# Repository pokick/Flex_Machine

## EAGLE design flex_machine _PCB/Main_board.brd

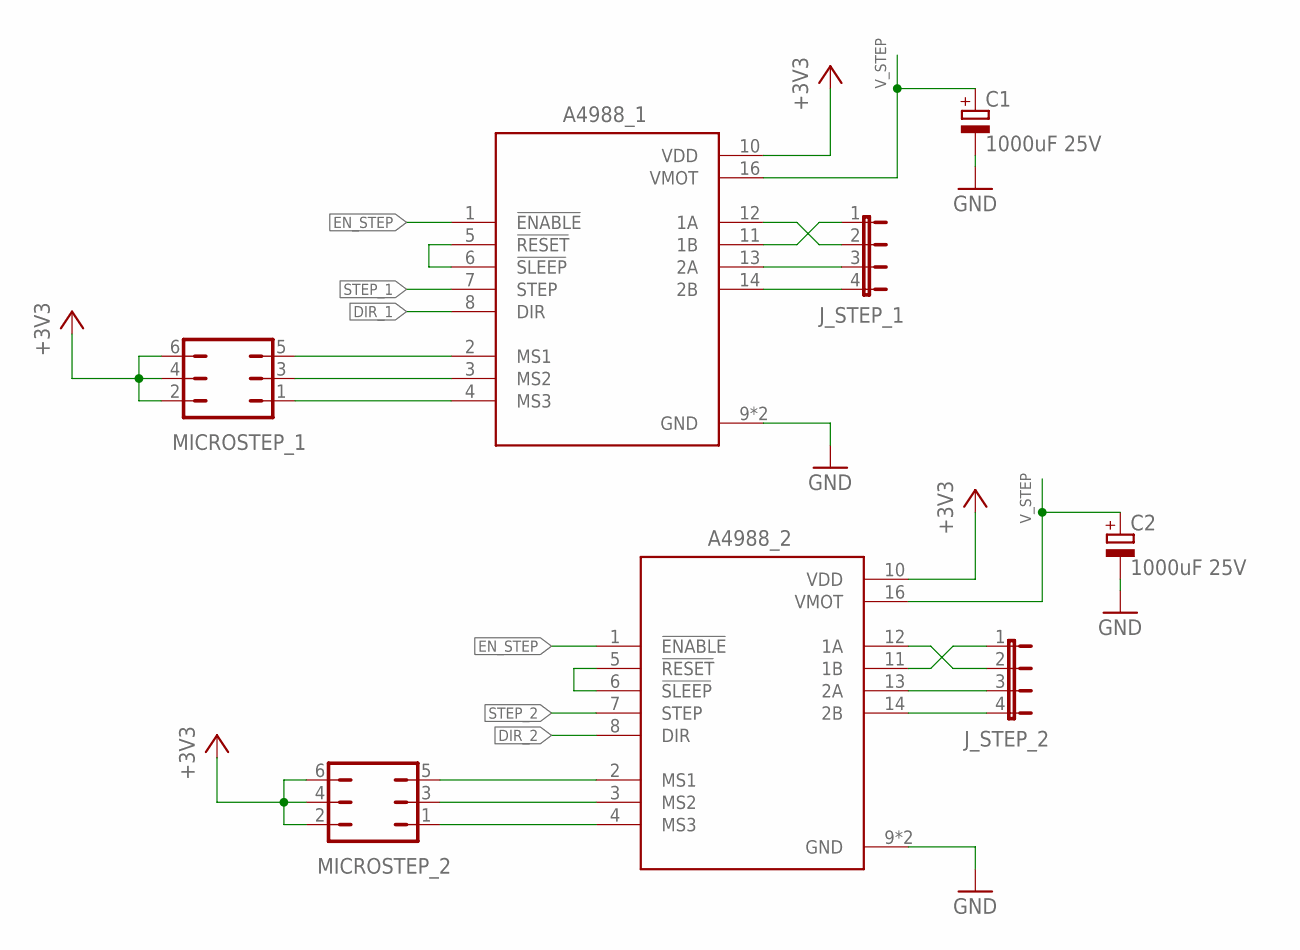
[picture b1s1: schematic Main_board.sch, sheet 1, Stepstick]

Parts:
A4988_1, A4988_2: A4988_STEPPER_MOTOR_DRIVER_CARRIER; MODULE_A4988_STEPPER_MOTOR_DRIVER_CARRIER
C1, C2: 1000uF 25V; E3,5-10
J_STEP_1, J_STEP_2: JP4E; JP4
MICROSTEP_1, MICROSTEP_2: JP3Q

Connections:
+3V3: A4988_1.10 (VDD), A4988_2.10 (VDD), MICROSTEP_1.2, MICROSTEP_1.4, MICROSTEP_1.6, MICROSTEP_2.2, MICROSTEP_2.4, MICROSTEP_2.6; also elsewhere on the board
DIR_1: A4988_1.8 (DIR); also elsewhere on the board
DIR_2: A4988_2.8 (DIR); also elsewhere on the board
EN_STEP: A4988_1.1 (!ENABLE), A4988_2.1 (!ENABLE); also elsewhere on the board
GND: A4988_1.9 (GND), A4988_1.15 (GND), A4988_2.9 (GND), A4988_2.15 (GND), C1.-, C2.-; also elsewhere on the board
unnamed: A4988_1.5 (!RESET), A4988_1.6 (!SLEEP)
unnamed: A4988_1.2 (MS1), MICROSTEP_1.5
unnamed: A4988_1.3 (MS2), MICROSTEP_1.3
unnamed: A4988_1.4 (MS3), MICROSTEP_1.1
unnamed: A4988_1.11 (1B), J_STEP_1.1
unnamed: A4988_1.12 (1A), J_STEP_1.2
unnamed: A4988_1.13 (2A), J_STEP_1.3
unnamed: A4988_1.14 (2B), J_STEP_1.4
unnamed: A4988_2.2 (MS1), MICROSTEP_2.5
unnamed: A4988_2.3 (MS2), MICROSTEP_2.3
unnamed: A4988_2.4 (MS3), MICROSTEP_2.1
unnamed: A4988_2.5 (!RESET), A4988_2.6 (!SLEEP)
unnamed: A4988_2.11 (1B), J_STEP_2.1
unnamed: A4988_2.12 (1A), J_STEP_2.2
unnamed: A4988_2.13 (2A), J_STEP_2.3
unnamed: A4988_2.14 (2B), J_STEP_2.4
STEP_1: A4988_1.7 (STEP); also elsewhere on the board
STEP_2: A4988_2.7 (STEP); also elsewhere on the board
V_STEP: A4988_1.16 (VMOT), A4988_2.16 (VMOT), C1.+, C2.+; also elsewhere on the board

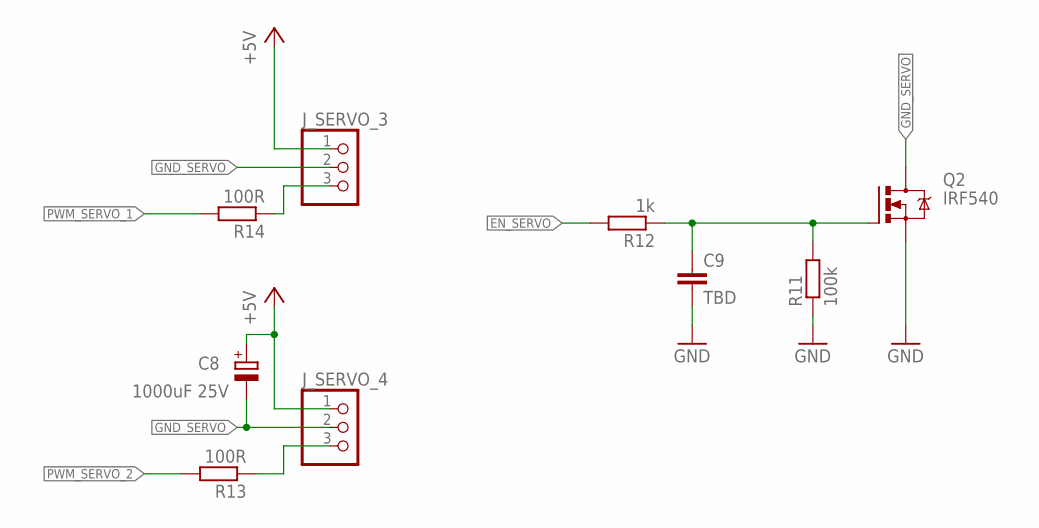
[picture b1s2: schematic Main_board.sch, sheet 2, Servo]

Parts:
C8: 1000uF 25V; E3,5-10
C9: TBD; C3216
J_SERVO_3, J_SERVO_4: PINHD-1X3; 1X03
Q2: IRF540; TO220BV
R11: 100k; R3216
R12: 1k; R3216
R13, R14: 100R; R3216

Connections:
+5V: C8.+, J_SERVO_3.1, J_SERVO_4.1; also elsewhere on the board
EN_SERVO: R12.2; also elsewhere on the board
GND: C9.2, Q2.S, R11.1; also elsewhere on the board
GND_SERVO: C8.-, J_SERVO_3.2, J_SERVO_4.2, Q2.D
unnamed: C9.1, Q2.G, R11.2, R12.1
unnamed: J_SERVO_4.3, R13.1
unnamed: J_SERVO_3.3, R14.1
PWM_SERVO_1: R14.2; also elsewhere on the board
PWM_SERVO_2: R13.2; also elsewhere on the board

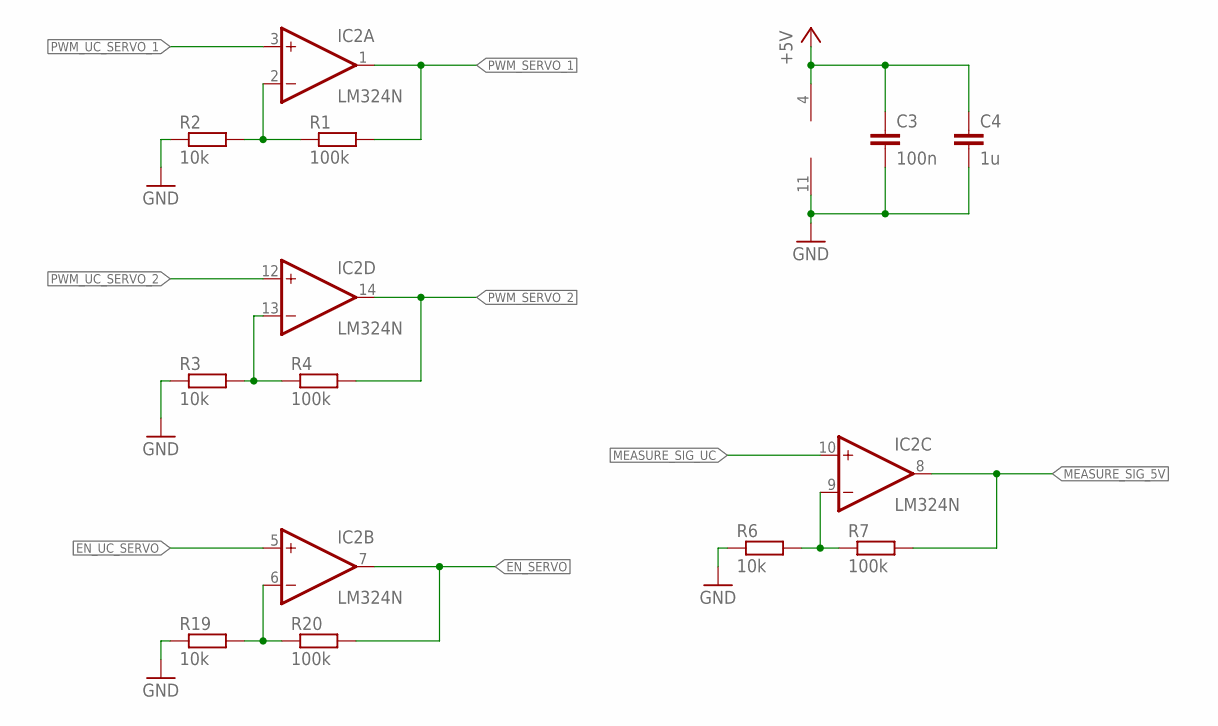
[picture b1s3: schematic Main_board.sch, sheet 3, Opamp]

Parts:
C3: 100n; C2012
C4: 1u; C2012
IC2: LM324N; DIL14
R1, R4, R7, R20: 100k; R3216
R2, R3, R6, R19: 10k; R3216

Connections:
+5V: C3.1, C4.1, IC2.4 (V+); also elsewhere on the board
EN_SERVO: IC2.7 (OUT), R20.2; also elsewhere on the board
EN_UC_SERVO: IC2.5 (+IN); also elsewhere on the board
GND: C3.2, C4.2, IC2.11 (V-), R2.1, R3.1, R6.1, R19.1; also elsewhere on the board
MEASURE_SIG_5V: IC2.8 (OUT), R7.2; also elsewhere on the board
MEASURE_SIG_UC: IC2.10 (+IN); also elsewhere on the board
unnamed: IC2.6 (-IN), R19.2, R20.1
unnamed: IC2.13 (-IN), R3.2, R4.1
unnamed: IC2.2 (-IN), R1.1, R2.2
unnamed: IC2.9 (-IN), R6.2, R7.1
PWM_SERVO_1: IC2.1 (OUT), R1.2; also elsewhere on the board
PWM_SERVO_2: IC2.14 (OUT), R4.2; also elsewhere on the board
PWM_UC_SERVO_1: IC2.3 (+IN); also elsewhere on the board
PWM_UC_SERVO_2: IC2.12 (+IN); also elsewhere on the board

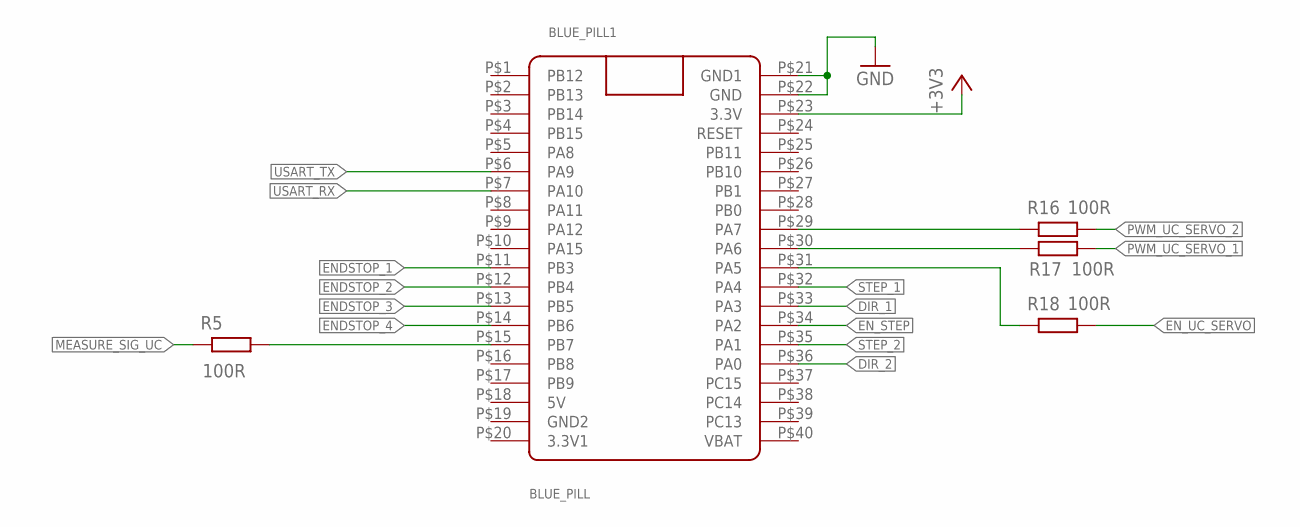
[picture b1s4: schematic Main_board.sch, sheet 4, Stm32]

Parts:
BLUE_PILL1: BLUE_PILL
R5, R16, R17, R18: 100R; R3216

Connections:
+3V3: BLUE_PILL1.P$23 (3.3V); also elsewhere on the board
DIR_1: BLUE_PILL1.P$33 (PA3); also elsewhere on the board
DIR_2: BLUE_PILL1.P$36 (PA0); also elsewhere on the board
ENDSTOP_1: BLUE_PILL1.P$11 (PB3); also elsewhere on the board
ENDSTOP_2: BLUE_PILL1.P$12 (PB4); also elsewhere on the board
ENDSTOP_3: BLUE_PILL1.P$13 (PB5); also elsewhere on the board
ENDSTOP_4: BLUE_PILL1.P$14 (PB6); also elsewhere on the board
EN_STEP: BLUE_PILL1.P$34 (PA2); also elsewhere on the board
EN_UC_SERVO: R18.2; also elsewhere on the board
GND: BLUE_PILL1.P$21 (GND1), BLUE_PILL1.P$22 (GND); also elsewhere on the board
MEASURE_SIG_UC: R5.1; also elsewhere on the board
unnamed: BLUE_PILL1.P$29 (PA7), R16.1
unnamed: BLUE_PILL1.P$31 (PA5), R18.1
unnamed: BLUE_PILL1.P$15 (PB7), R5.2
unnamed: BLUE_PILL1.P$30 (PA6), R17.1
PWM_UC_SERVO_1: R17.2; also elsewhere on the board
PWM_UC_SERVO_2: R16.2; also elsewhere on the board
STEP_1: BLUE_PILL1.P$32 (PA4); also elsewhere on the board
STEP_2: BLUE_PILL1.P$35 (PA1); also elsewhere on the board
USART_RX: BLUE_PILL1.P$7 (PA10); also elsewhere on the board
USART_TX: BLUE_PILL1.P$6 (PA9); also elsewhere on the board

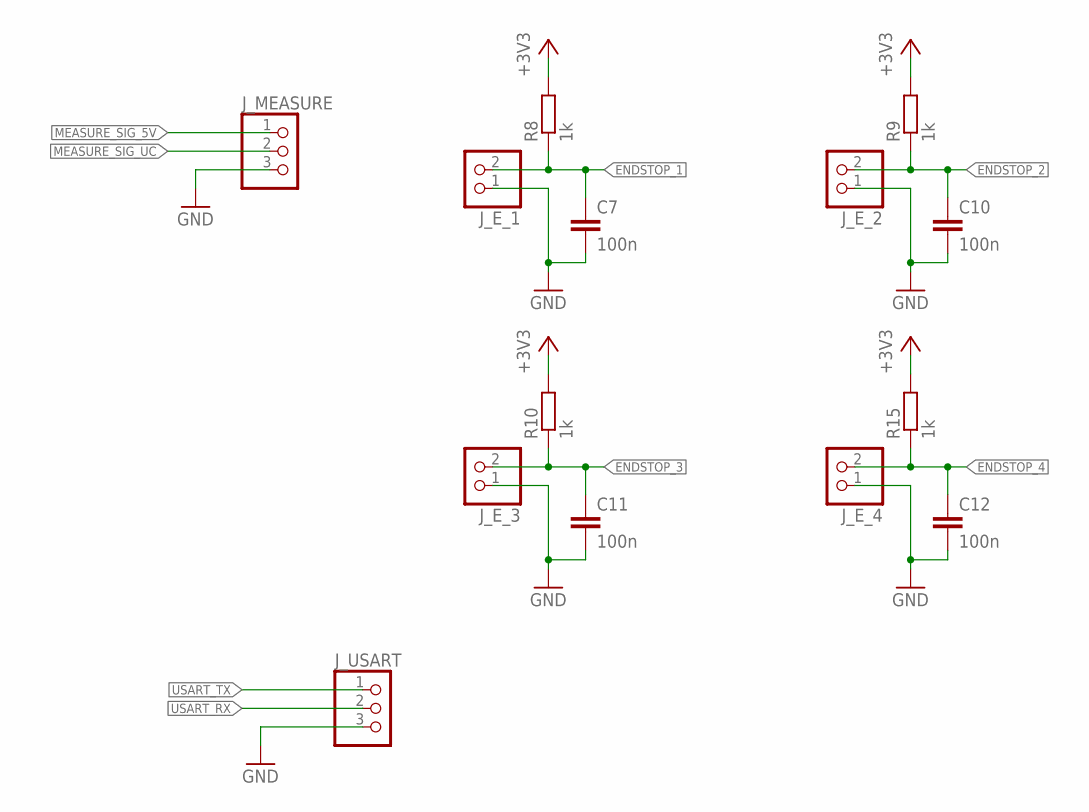
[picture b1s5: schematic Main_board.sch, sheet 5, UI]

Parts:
C7, C10, C11, C12: 100n; C0402
J_E_1, J_E_2, J_E_3, J_E_4: PINHD-1X2; 1X02
J_MEASURE: PINHD-1X3; 1X03
J_USART: PINHD-1X3; 1X03
R8, R9, R10, R15: 1k; R3216

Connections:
+3V3: R8.2, R9.2, R10.2, R15.2; also elsewhere on the board
ENDSTOP_1: C7.1, J_E_1.2, R8.1; also elsewhere on the board
ENDSTOP_2: C10.1, J_E_2.2, R9.1; also elsewhere on the board
ENDSTOP_3: C11.1, J_E_3.2, R10.1; also elsewhere on the board
ENDSTOP_4: C12.1, J_E_4.2, R15.1; also elsewhere on the board
GND: C7.2, C10.2, C11.2, C12.2, J_E_1.1, J_E_2.1, J_E_3.1, J_E_4.1, J_MEASURE.3, J_USART.3; also elsewhere on the board
MEASURE_SIG_5V: J_MEASURE.1; also elsewhere on the board
MEASURE_SIG_UC: J_MEASURE.2; also elsewhere on the board
USART_RX: J_USART.2; also elsewhere on the board
USART_TX: J_USART.1; also elsewhere on the board

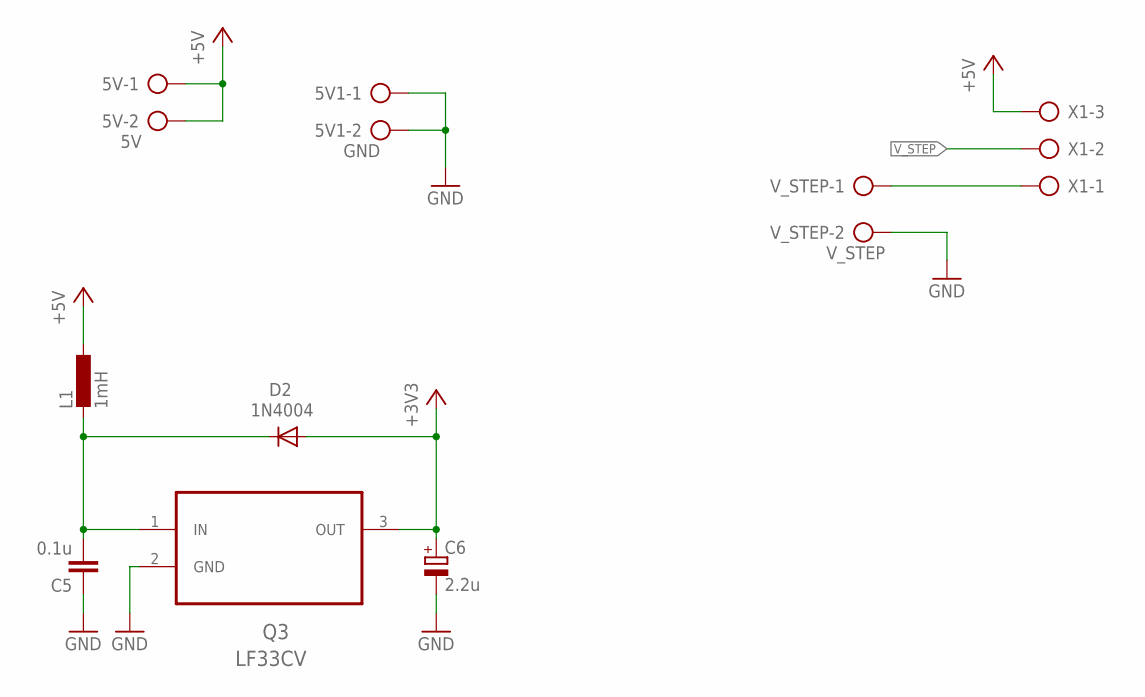
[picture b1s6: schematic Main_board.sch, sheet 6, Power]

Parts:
5V: 5V; AK500/2
5V1: GND; AK500/2
C5: 0.1u; C3216
C6: 2.2u; E2,5-5
D2: 1N4004; DO41-10
L1: 1mH; POWER-CHOKE_WE-TPC
Q3: LF33CV; TO254P450X1020X1935-3P
V_STEP: V_STEP; AK500/2
X1: AK500/3-H

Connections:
+3V3: C6.+, D2.A, Q3.3 (OUT); also elsewhere on the board
+5V: 5V.1, 5V.2, L1.1, X1.3; also elsewhere on the board
GND: 5V1.1, 5V1.2, C5.1, C6.-, Q3.2 (GND), V_STEP.2; also elsewhere on the board
unnamed: V_STEP.1, X1.1
unnamed: C5.2, D2.C, L1.2, Q3.1 (IN)
V_STEP: X1.2; also elsewhere on the board

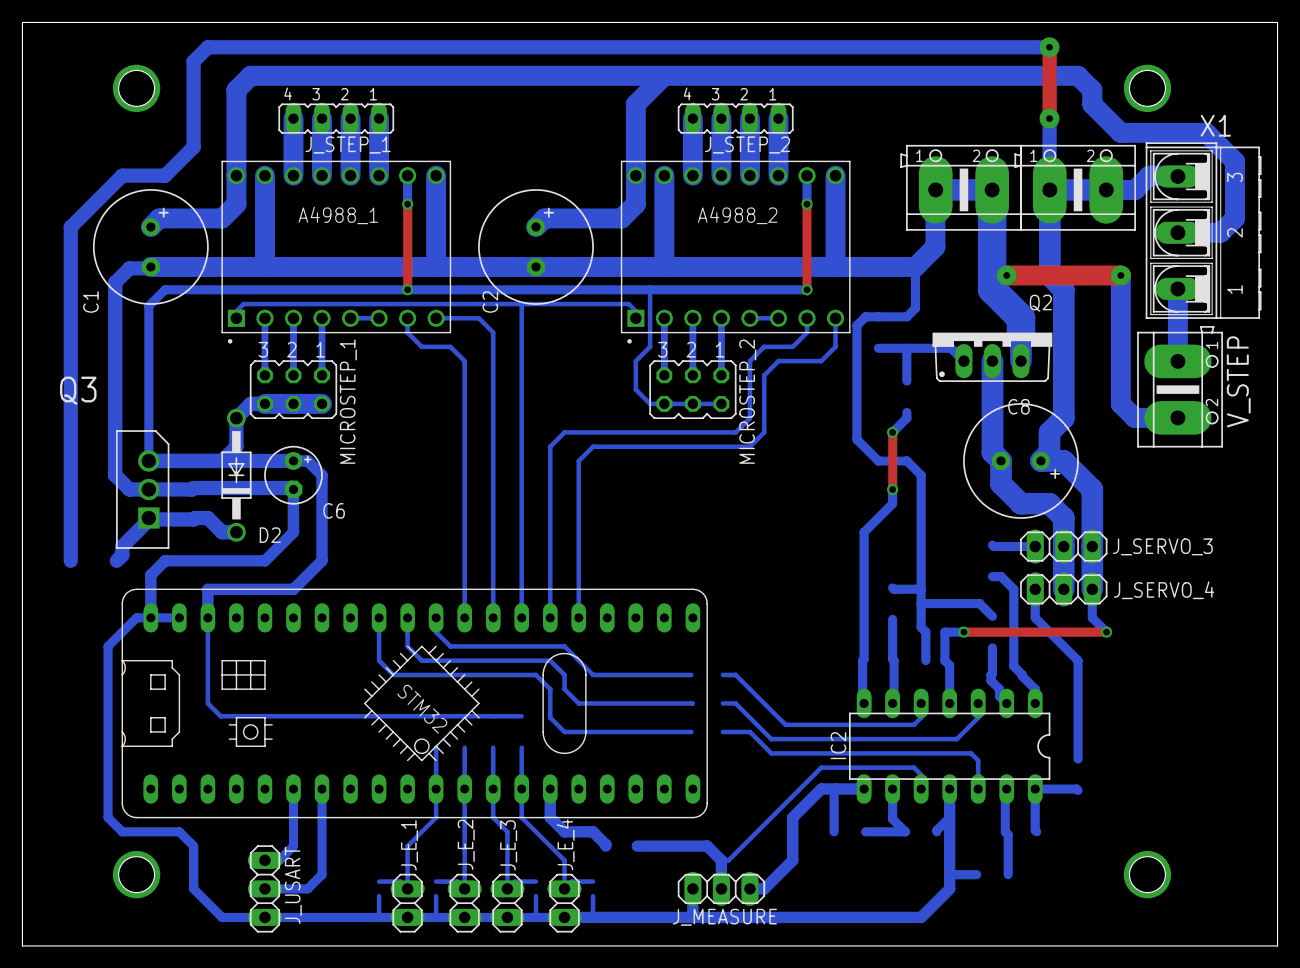
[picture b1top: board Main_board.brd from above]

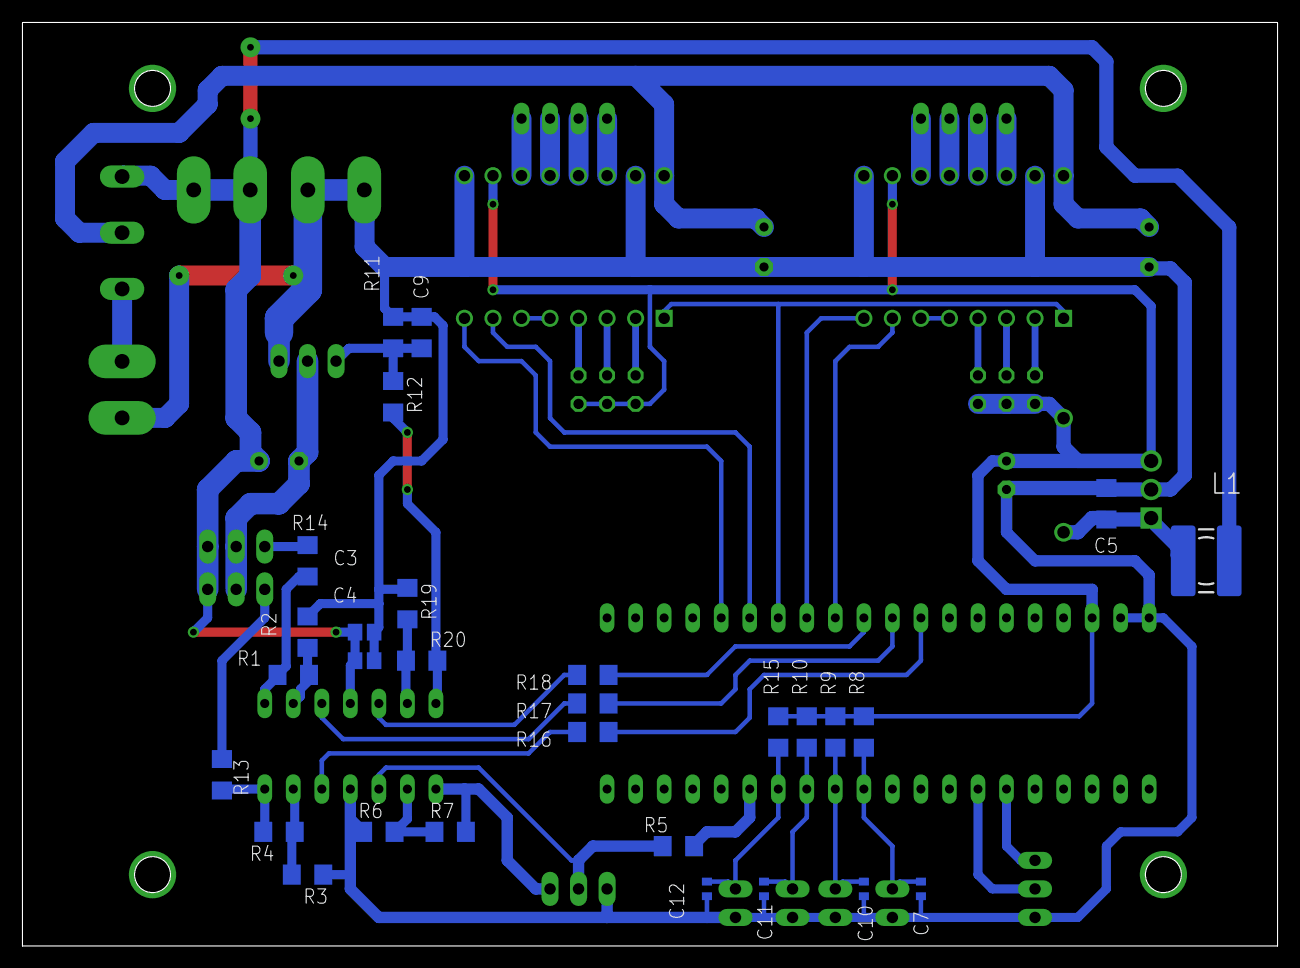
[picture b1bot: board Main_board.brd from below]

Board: 2 copper layers, 111.7 x 82.2 mm, 56 parts (29 on the bottom side), 53 nets.

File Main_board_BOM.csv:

"Qty";"Value";"Device";"Package";"Parts";"Description";"AVAILABILITY";"DESCRIPTION";"MF";"MP";"MPN";"OC_FARNELL";"OC_NEWARK";"PACKAGE";"PRICE";"PURCHASE-URL";
"1";"";"AK500/3-H";"AK500/3-H";"X1";"CONNECTOR";"";"";"";"";"";"unknown";"unknown";"";"";"";
"2";"";"JP3Q";"JP3Q";"MICROSTEP_1, MICROSTEP_2";"JUMPER";"";"";"";"";"";"";"";"";"";"";
"2";"";"JP4E";"JP4";"J_STEP_1, J_STEP_2";"JUMPER";"";"";"";"";"";"";"";"";"";"";
"4";"";"PINHD-1X2";"1X02";"J_ENDSTOP_1, J_ENDSTOP_2, J_ENDSTOP_3, J_ENDSTOP_4";"PIN HEADER";"";"";"";"";"";"";"";"";"";"";
"4";"";"PINHD-1X3";"1X03";"J_MEASURE, J_SERVO_3, J_SERVO_4, J_USART";"PIN HEADER";"";"";"";"";"";"";"";"";"";"";
"1";"0.1u";"C-EUC3216";"C3216";"C5";"CAPACITOR, European symbol";"";"";"";"";"";"";"";"";"";"";
"3";"1000uF 25V";"CPOL-EUE3.5-10";"E3,5-10";"C1, C2, C8";"POLARIZED CAPACITOR, European symbol";"";"";"";"";"";"";"";"";"";"";
"6";"100R";"R-EU_R3216";"R3216";"R5, R13, R14, R16, R17, R18";"RESISTOR, European symbol";"";"";"";"";"";"";"";"";"";"";
"5";"100k";"R-EU_R3216";"R3216";"R1, R4, R7, R11, R20";"RESISTOR, European symbol";"";"";"";"";"";"";"";"";"";"";
"4";"100n";"C-EUC0402";"C0402";"C7, C10, C11, C12";"CAPACITOR, European symbol";"";"";"";"";"";"";"";"";"";"";
"1";"100n";"C-EUC2012";"C2012";"C3";"CAPACITOR, European symbol";"";"";"";"";"";"";"";"";"";"";
"4";"10k";"R-EU_R3216";"R3216";"R2, R3, R6, R19";"RESISTOR, European symbol";"";"";"";"";"";"";"";"";"";"";
"1";"1N4004";"1N4004";"DO41-10";"D2";"DIODE";"";"";"";"";"";"";"";"";"";"";
"5";"1k";"R-EU_R3216";"R3216";"R8, R9, R10, R12, R15";"RESISTOR, European symbol";"";"";"";"";"";"";"";"";"";"";
"1";"1mH";"L-EUWE-TPC";"POWER-CHOKE_WE-TPC";"L1";"INDUCTOR, European symbol";"";"";"";"";"";"";"";"";"";"";
"1";"1u";"C-EUC2012";"C2012";"C4";"CAPACITOR, European symbol";"";"";"";"";"";"";"";"";"";"";
"1";"2.2u";"CPOL-EUE2.5-5";"E2,5-5";"C6";"POLARIZED CAPACITOR, European symbol";"";"";"";"";"";"";"";"";"";"";
"1";"5V";"AK500/2";"AK500/2";"5V";"CONNECTOR";"";"";"";"";"";"unknown";"unknown";"";"";"";
"2";"A4988_STEPPER_MOTOR_DRIVER_CARRIER";"A4988_STEPPER_MOTOR_DRIVER_CARRIER";"MODULE_A4988_STEPPER_MOTOR_DRIVER_CARRIER";"A4988_1, A4988_2";"Stepper motor controler; IC: A4988; 1A; Uin mot: 8÷35V Check prices";"Not in stock";" Stepper Motor Driver ";"Pololu";"A4988 STEPPER MOTOR DRIVER CARRIER";"";"";"";"None";"None";"";
"1";"BLUE_PILL";"BLUE_PILL";"BLUE_PILL";"BLUE_PILL1";"";"";"";"";"";"";"";"";"";"";"";
"1";"GND";"AK500/2";"AK500/2";"5V1";"CONNECTOR";"";"";"";"";"";"unknown";"unknown";"";"";"";
"1";"IRF540";"IRF540";"TO220BV";"Q2";"HEXFET Power MOSFET";"";"";"";"";"";"";"";"";"";"";
"1";"LF33CV";"LF33CV";"TO254P450X1020X1935-3P";"Q3";"Very low drop voltage regulators with inhibit Check prices";"In Stock";" Linear Voltage Regulator IC Positive Fixed 1 Output 500mA TO-220 ";"STMicroelectronics";"LF33CV";"";"";"";"TO-220-3 ON Semiconductor";"None";"https://pricing.snapeda.com/search/part/LF33CV/?ref=eda";
"1";"LM324N";"LM324N";"DIL14";"IC2";"OP AMP";"";"";"";"";"";"";"";"";"";"";
"1";"TBD";"C-EUC3216";"C3216";"C9";"CAPACITOR, European symbol";"";"";"";"";"";"";"";"";"";"";
"1";"V_STEP";"AK500/2";"AK500/2";"V_STEP";"CONNECTOR";"";"";"";"";"";"unknown";"unknown";"";"";"";

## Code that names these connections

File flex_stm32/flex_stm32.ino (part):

#include <Servo.h>

#define PIN_ENDSTOP_1 PB3
#define PIN_ENDSTOP_2 PB4
#define PIN_ENDSTOP_3 PB5
#define PIN_ENDSTOP_4 PB6

#define PIN_MEASURE PB7
#define PIN_SERVO_1 PA7
#define PIN_SERVO_2 PA6
#define PIN_EN_SERVO PA5
#define PIN_STEP_1 PA4
#define PIN_DIR_1 PA3
#define PIN_EN_STEP PA2
#define PIN_STEP_2 PA1
#define PIN_DIR_2 PA0

const int STEPS_PER_MM = 250; // for full rotaton
// compensate Servo 1 deg
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  Serial.begin(115200);
  Serial.println("BOOTING ...");
  //define all pins 
  pinMode(PIN_EN_STEP, OUTPUT);
  digitalWrite(PIN_EN_STEP, HIGH);
  pinMode(PIN_EN_SERVO, OUTPUT);
  digitalWrite(PIN_EN_SERVO, LOW);

  servo_1.attach(PIN_SERVO_1);
  servo_2.attach(PIN_SERVO_2);
  servo_1.write(90 + C_SERVO1);
  servo_2.write(90 + C_SERVO2);

  pinMode(PIN_ENDSTOP_1, INPUT);
  pinMode(PIN_ENDSTOP_2, INPUT);
  pinMode(PIN_ENDSTOP_3, INPUT);
  pinMode(PIN_ENDSTOP_4, INPUT);

  pinMode(PIN_MEASURE, OUTPUT);
  digitalWrite(PIN_MEASURE, LOW);
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  // digitalWrite(PIN_SERVO_1,LOW);
  //  pinMode(PIN_SERVO_2, OUTPUT);
  //digitalWrite(PIN_SERVO_2,LOW);
  pinMode(PIN_STEP_1, OUTPUT);
  digitalWrite(PIN_STEP_1, LOW);
  pinMode(PIN_DIR_1, OUTPUT);
  digitalWrite(PIN_DIR_1, LOW);
  pinMode(PIN_STEP_2, OUTPUT);
  digitalWrite(PIN_STEP_2, LOW);
  pinMode(PIN_DIR_2, OUTPUT);
  digitalWrite(PIN_DIR_2, LOW);

}

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
void home_step(void) {

  while (digitalRead(PIN_ENDSTOP_1) != 0) {
    _step(1, 1, 1);
  }
  while (digitalRead(PIN_ENDSTOP_2) != 0) {
    _step(2, 1, 1);
  }

  _step(1, 0, 250);
  _step(2, 0, 250);

  while (digitalRead(PIN_ENDSTOP_1) != 0) {
    _step(1, 1, 1);
    delay(15);
  }
  while (digitalRead(PIN_ENDSTOP_2) != 0) {
    _step(2, 1, 1);
    delay(15);
  }
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
    if (motor == 1) {
      if (dir == 0) {
        digitalWrite(PIN_DIR_1, LOW);
      } else {
        digitalWrite(PIN_DIR_1, HIGH);
      }

      digitalWrite(PIN_STEP_1, HIGH);
      delayMicroseconds(delay_time);
      digitalWrite(PIN_STEP_1, LOW);
      delayMicroseconds(delay_time);

    } else if (motor == 2) {
      if (dir == 0) {
        digitalWrite(PIN_DIR_2, LOW);
      } else {
        digitalWrite(PIN_DIR_2, HIGH);
      }

      digitalWrite(PIN_STEP_2, HIGH);
      delayMicroseconds(delay_time);
      digitalWrite(PIN_STEP_2, LOW);
      delayMicroseconds(delay_time);
    }
    steps--;
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
    while (steps > 0) {
      if (dir == 0) {
        digitalWrite(PIN_DIR_1, LOW);
        digitalWrite(PIN_DIR_2, LOW);
        stepper_position++;
      } else {
        digitalWrite(PIN_DIR_1, HIGH);
        digitalWrite(PIN_DIR_2, HIGH);
        stepper_position--;
      }

      digitalWrite(PIN_STEP_1, HIGH);
      digitalWrite(PIN_STEP_2, HIGH);
      delayMicroseconds(delay_time);
      digitalWrite(PIN_STEP_1, LOW);
      digitalWrite(PIN_STEP_2, LOW);
      delayMicroseconds(delay_time);

      // Serial.println(stepper_position);
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}

void arm(void) {
  digitalWrite(PIN_EN_STEP, LOW);
  digitalWrite(PIN_EN_SERVO, HIGH);

}

void disarm(void) {
  digitalWrite(PIN_EN_STEP, HIGH);
  digitalWrite(PIN_EN_SERVO, LOW);

}

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
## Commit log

2022-06-19 Rename script.py to GUI_Raspberry.py
2022-06-19 Create 3d_Models_Inventor
